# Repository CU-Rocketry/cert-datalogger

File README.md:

# cert-datalogger

Eggtimer Ion replica using ESP32-C3

## Features

- ESP32 MCU with WiFi and Bluetooth control and data export
- Pressure and temperature measurement
- 3.7V lithium battery compatibility
- Status LED and Buzzer

## Images

Screenshots for now:

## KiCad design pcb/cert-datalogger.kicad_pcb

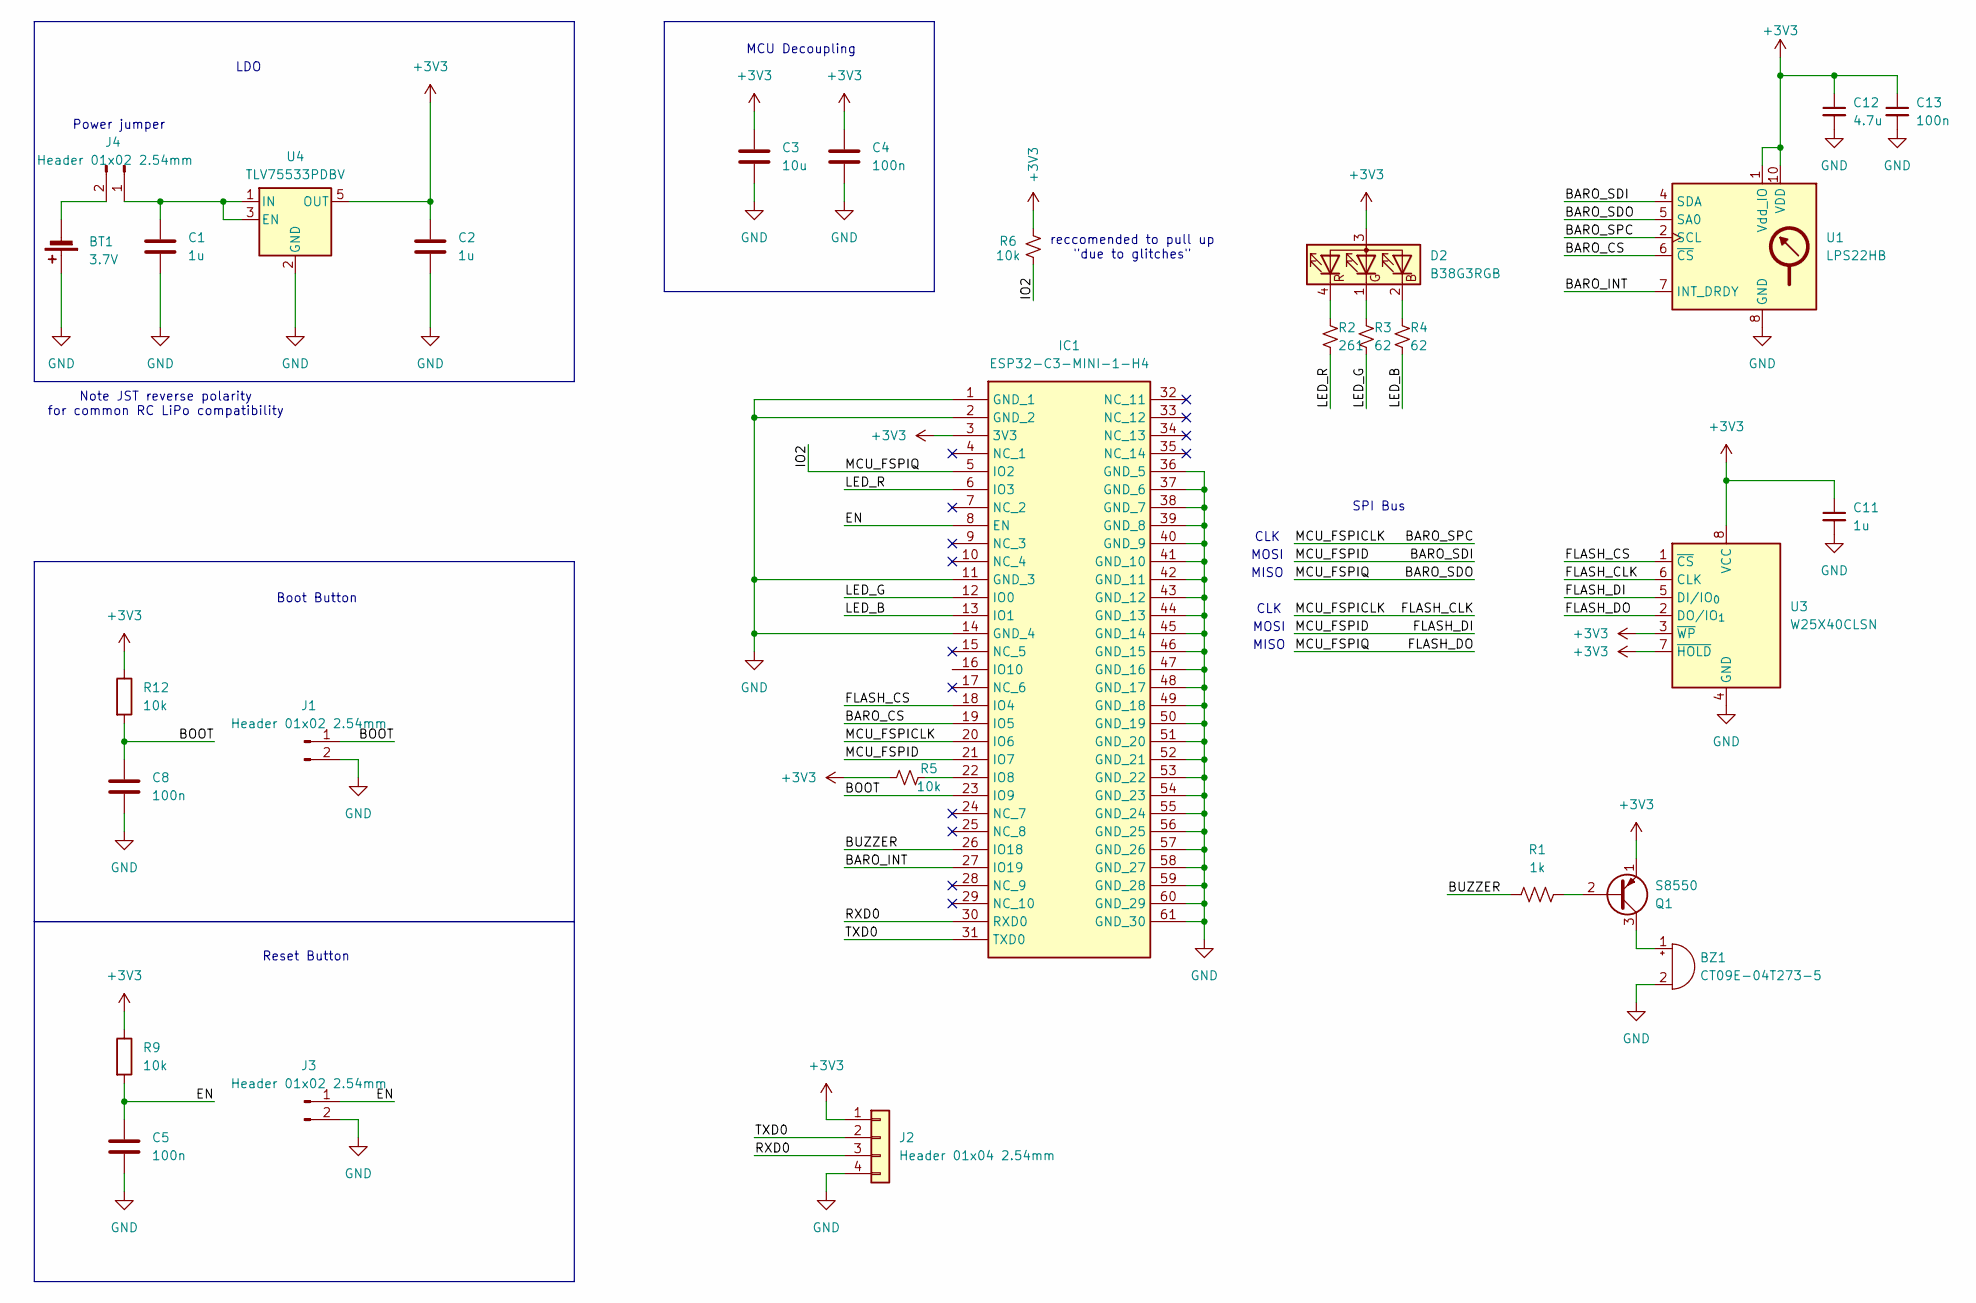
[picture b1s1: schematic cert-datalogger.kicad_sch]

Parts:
BT1: 3.7V; JST_PH_B2B-PH-K_1x02_P2.00mm_Vertical
BZ1: CT09E-04T273-5
C1, C2, C11: 1u; C_0603_1608Metric
C3: 10u; C_0603_1608Metric
C4, C5, C8, C13: 100n; C_0603_1608Metric
C12: 4.7u; C_0603_1608Metric
D2: B38G3RGB; B38G3RGB-10D0003H2U1930_HVK
IC1: ESP32-C3-MINI-1-H4; Mouser Part Number 356-ESP32-C3-MINI1H4
J1, J3, J4: Header 01x02 2.54mm; PinHeader_1x02_P2.54mm_Vertical
J2: Header 01x04 2.54mm; PinHeader_1x04_P2.54mm_Vertical
Q1: S8550; SOT-23
R1: 1k; R_0603_1608Metric
R2: 261; R_0603_1608Metric
R3, R4: 62; R_0603_1608Metric
R5, R6, R9, R12: 10k; R_0603_1608Metric
U1: LPS22HB; ST_HLGA-10_2x2mm_P0.5mm_LayoutBorder3x2y
U3: W25X40CLSN; SOIC-8_3.9x4.9mm_P1.27mm
U4: TLV75533PDBV; SOT-23-5

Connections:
+3V3: C2.1, C3.1, C4.1, C11.1, C12.1, C13.1, D2.3 (A), IC1.3 (3V3), J2.1, Q1.1 (E), R5.1, R6.1, R9.1, R12.1, U1.1 (Vdd_IO), U1.10 (VDD), U3.3 (~WP), U3.7 (~HOLD), U3.8 (VCC), U4.5 (OUT)
/BARO_CS: IC1.19 (IO5), U1.6 (~CS)
/BARO_INT: IC1.27 (IO19), U1.7 (INT_DRDY)
/BARO_SDI: IC1.21 (IO7), U1.4 (SDA), U3.5 (DI/IO_{0})
/BARO_SDO: IC1.5 (IO2), R6.2, U1.5 (SA0), U3.2 (DO/IO_{1})
/BARO_SPC: IC1.20 (IO6), U1.2 (SCL), U3.6 (CLK)
/BOOT: C8.1, IC1.23 (IO9), J1.1, R12.2
/BUZZER: IC1.26 (IO18), R1.1
/EN: C5.1, IC1.8 (EN), J3.1, R9.2
/FLASH_CS: IC1.18 (IO4), U3.1 (~CS)
/LED_B: IC1.13 (IO1), R4.2
/LED_G: IC1.12 (IO0), R3.2
/LED_R: IC1.6 (IO3), R2.2
/RXD0: IC1.30 (RXD0), J2.3
/TXD0: IC1.31 (TXD0), J2.2
GND: BT1.1 (+), BZ1.2 (-), C1.2, C2.2, C3.2, C4.2, C5.2, C8.2, C11.2, C12.2, C13.2, IC1.1 (GND_1), IC1.2 (GND_2), IC1.11 (GND_3), IC1.14 (GND_4), IC1.36 (GND_5), IC1.37 (GND_6), IC1.38 (GND_7), IC1.39 (GND_8), IC1.40 (GND_9), IC1.41 (GND_10), IC1.42 (GND_11), IC1.43 (GND_12), IC1.44 (GND_13), IC1.45 (GND_14), IC1.46 (GND_15), IC1.47 (GND_16), IC1.48 (GND_17), IC1.49 (GND_18), IC1.50 (GND_19), IC1.51 (GND_20), IC1.52 (GND_21), IC1.53 (GND_22), IC1.54 (GND_23), IC1.55 (GND_24), IC1.56 (GND_25), IC1.57 (GND_26), IC1.58 (GND_27), IC1.59 (GND_28), IC1.60 (GND_29), IC1.61 (GND_30), J1.2, J2.4, J3.2, U1.3 (GND), U1.8 (GND), U1.9 (GND), U3.4 (GND), U4.2 (GND)
unnamed: BT1.2 (-), J4.2
unnamed: BZ1.1 (+), Q1.3 (C)
unnamed: D2.2 (BK), R4.1
unnamed: D2.1 (GK), R3.1
unnamed: D2.4 (RK), R2.1
unnamed: IC1.22 (IO8), R5.2
unnamed: C1.1, J4.1, U4.1 (IN), U4.3 (EN)
unnamed: Q1.2 (B), R1.2

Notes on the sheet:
Reset Button
SPI Bus
MISO
LDO
Power jumper
Boot Button
reccomended to pull up "due to glitches"
Note JST reverse polarity for common RC LiPo compatibility
CLK
MOSI
MCU Decoupling

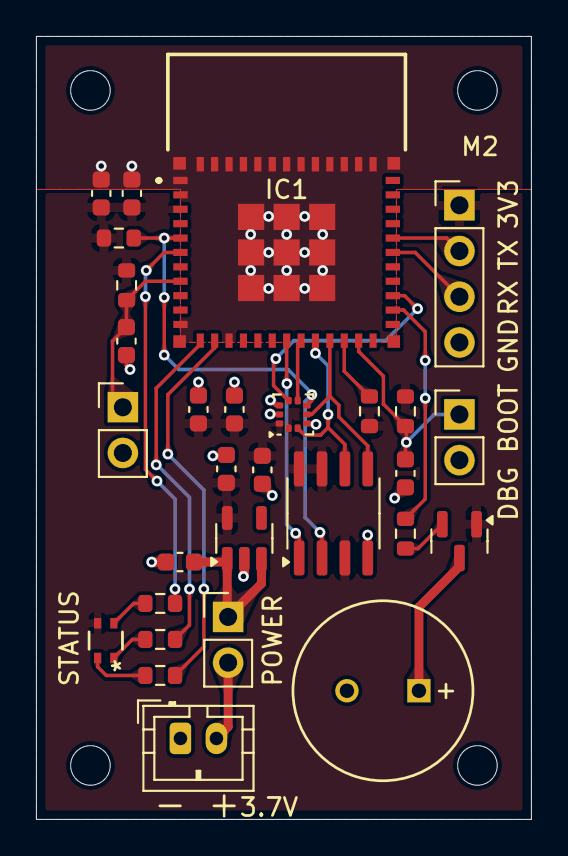
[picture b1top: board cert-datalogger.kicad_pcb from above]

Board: 2 copper layers, 27.5 x 43.5 mm, 29 parts (0 on the bottom side), 24 nets.

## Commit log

2025-03-31 Add PCB
2025-03-31 Add src
2025-03-31 Update kicad-library-sigmondkukla
2025-03-31 Add readme and screenshots
2025-03-31 Fix screenshots
2025-03-31 Fix ESP32 3D model
2025-03-31 Rearrange screenshots
